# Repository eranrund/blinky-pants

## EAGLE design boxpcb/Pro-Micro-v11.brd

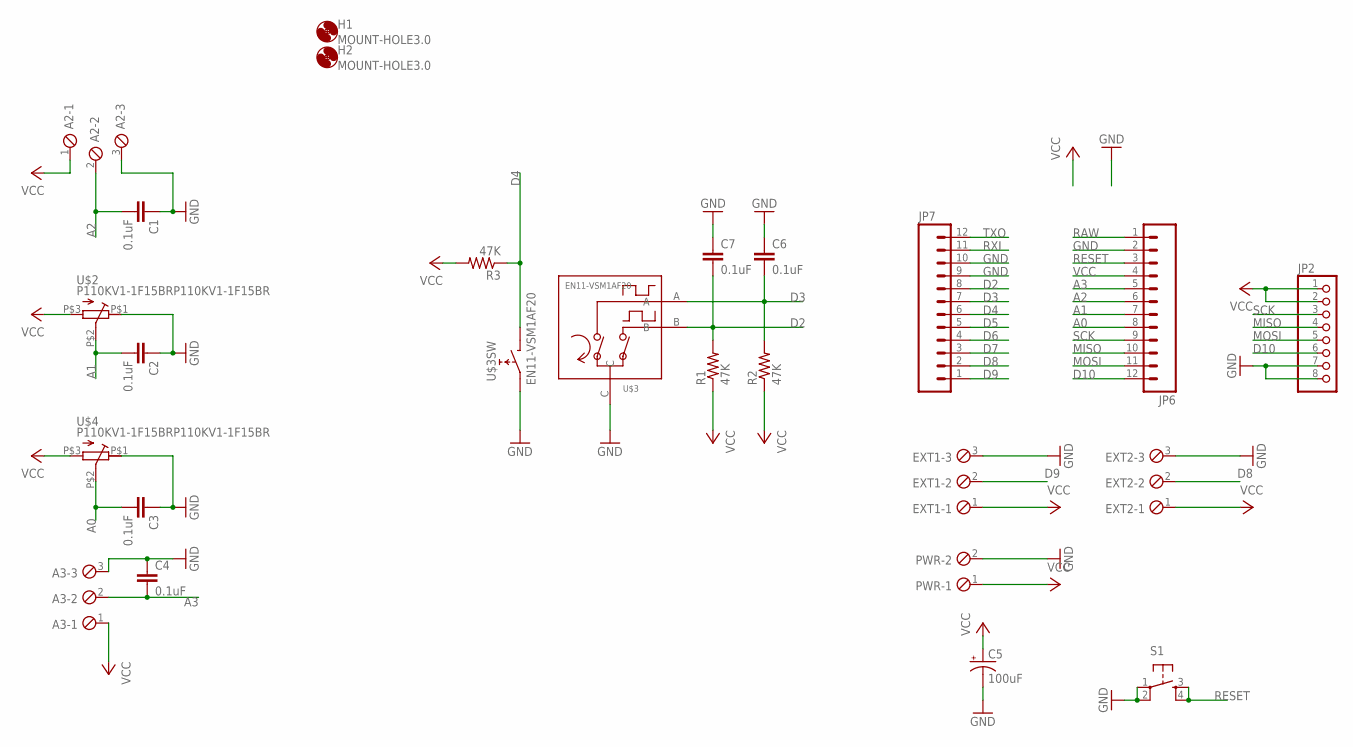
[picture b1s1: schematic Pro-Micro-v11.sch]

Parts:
A2, A3: MPT3; 3POL254
C1, C2, C3, C4: 0.1uF; C025-025X050
C5: 100uF; E3,5-8
C6, C7: 0.1uF; C025-024X044
EXT1, EXT2: MPT3; 3POL254
H1, H2: MOUNT-HOLE3.0; 3,0
JP2: HEADER-1X8; 1X08_OVAL
JP6, JP7: M12PTH; 1X12
PWR: MPT2; 2POL254
R1, R2, R3: 47K; 0204/5
S1: TAC_SWITCHPTH; TACTILE-PTH
U$2, U$4: P110KV1-1F15BRP110KV1-1F15BR; P110KV1-1F15BR
U$3: EN11-VSM1AF20; EN11-VS*

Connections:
A0: C3.2, JP6.8, U$4.P$2 (S)
A1: C2.2, JP6.7, U$2.P$2 (S)
A2: A2.2, C1.2, JP6.6
A3: A3.2, C4.2, JP6.5
D2: C7.2, JP7.8, R1.2, U$3.B
D3: C6.2, JP7.7, R2.2, U$3.A
D4: JP7.6, R3.1, U$3.E
D5: JP7.5
D6: JP7.4
D7: JP7.3
D8: EXT2.2, JP7.2
D9: EXT1.2, JP7.1
D10: JP2.6, JP6.12
GND: A2.3, A3.3, C1.1, C2.1, C3.1, C4.1, C5.-, C6.1, C7.1, EXT1.3, EXT2.3, JP2.7, JP2.8, JP6.2, JP7.9, JP7.10, PWR.2, S1.1, S1.2, U$2.P$1 (A), U$3.C, U$3.D, U$4.P$1 (A)
MISO: JP2.4, JP6.10
MOSI: JP2.5, JP6.11
RAW: JP6.1
RESET: JP6.3, S1.3, S1.4
RXI: JP7.11
SCK: JP2.3, JP6.9
TXO: JP7.12
VCC: A2.1, A3.1, C5.+, EXT1.1, EXT2.1, JP2.1, JP2.2, JP6.4, PWR.1, R1.1, R2.1, R3.2, U$2.P$3 (E), U$4.P$3 (E)

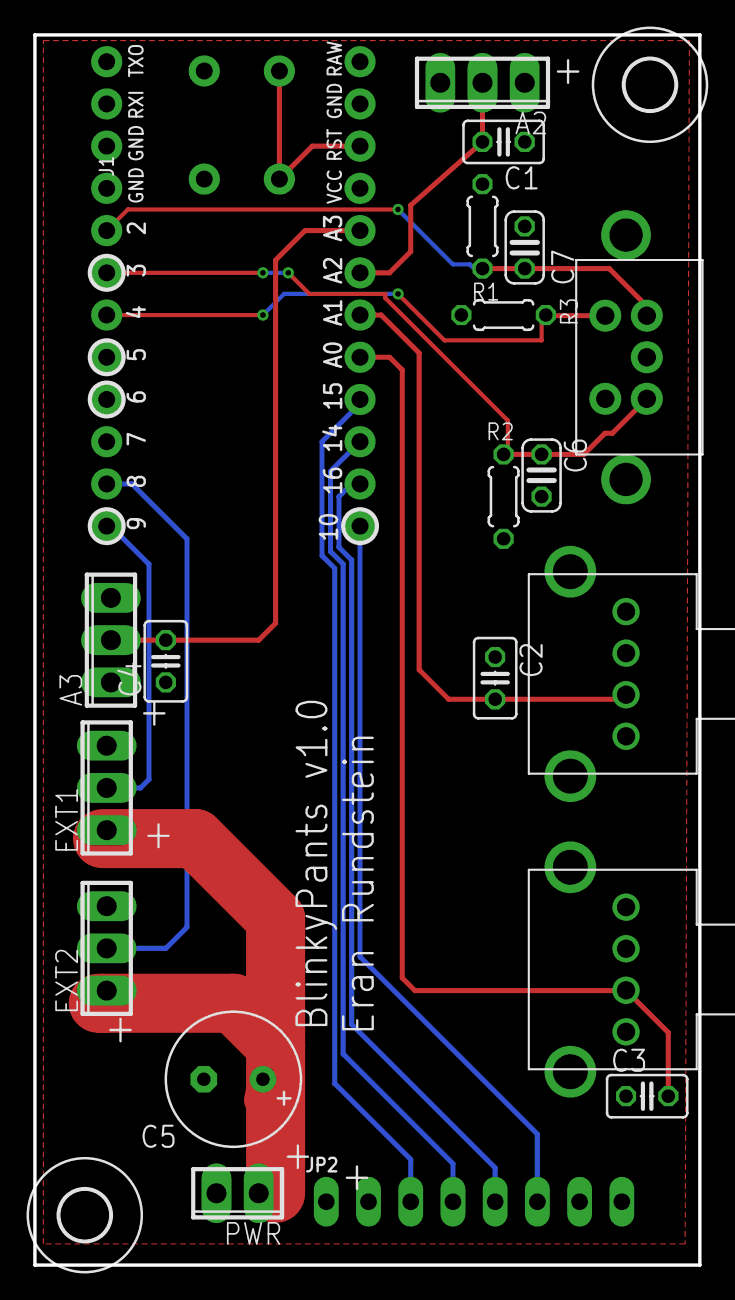
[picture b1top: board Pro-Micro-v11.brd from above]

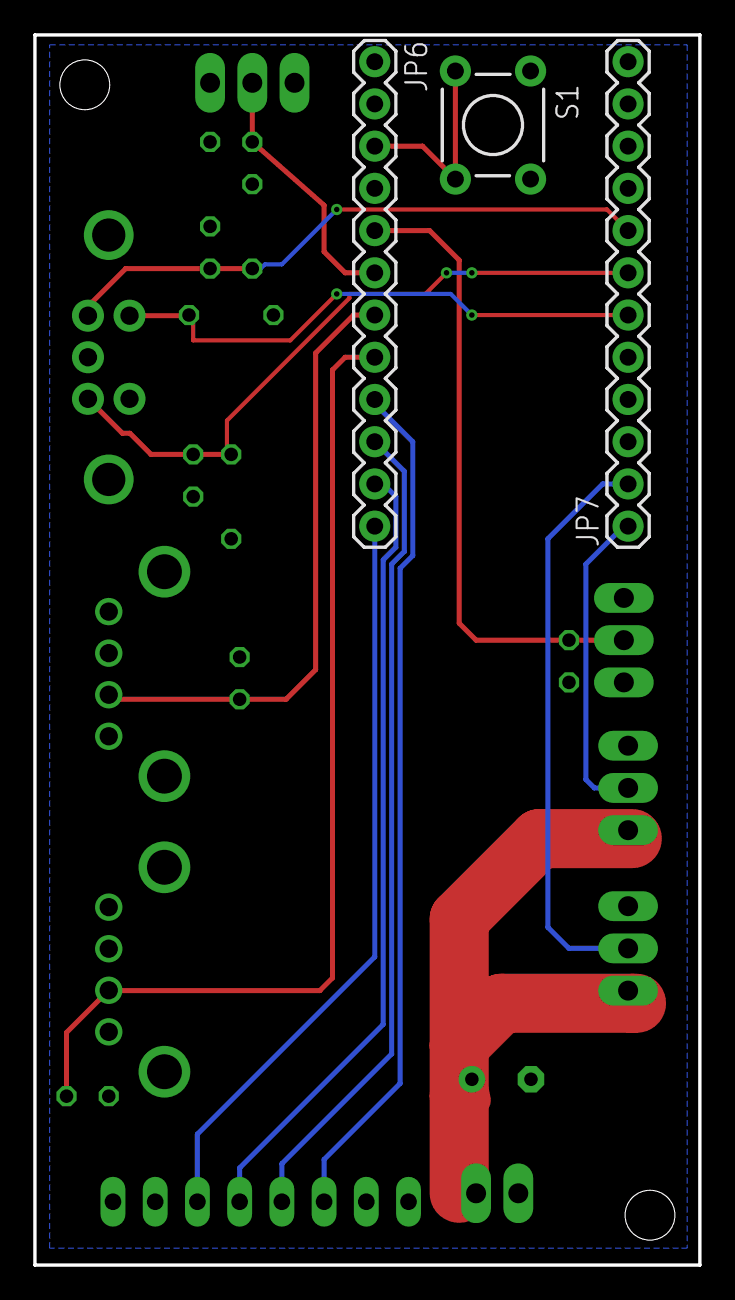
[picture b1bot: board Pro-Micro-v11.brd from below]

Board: 2 copper layers, 40.0 x 74.0 mm, 24 parts (3 on the bottom side), 16 nets.

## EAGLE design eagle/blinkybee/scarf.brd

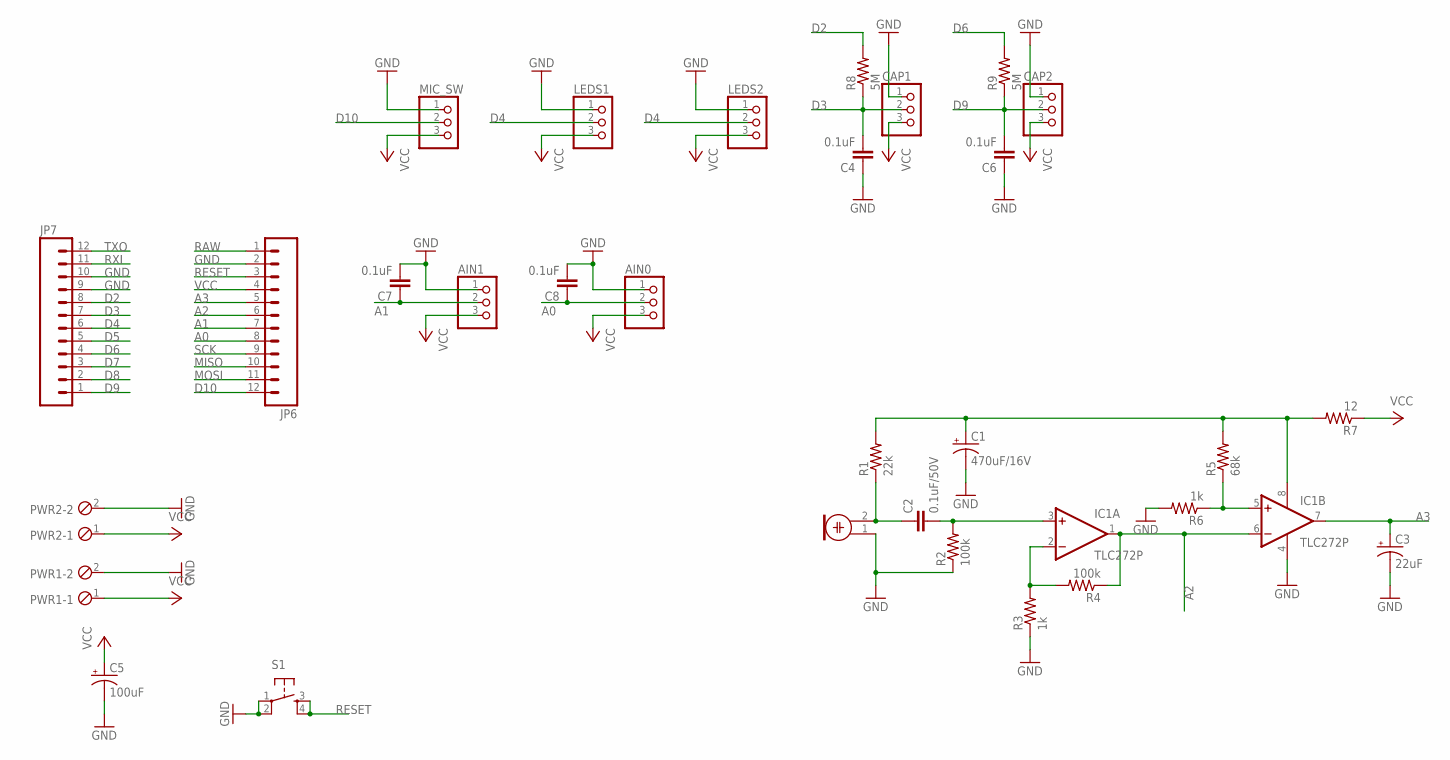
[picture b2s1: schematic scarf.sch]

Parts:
AIN0, AIN1: HEADER-1X3ROUND; 1X03_ROUND
C1: 470uF/16V; E2,5-6
C2: 0.1uF/50V; C050-025X075
C3: 22uF; E2,5-6
C4, C6, C7, C8: 0.1uF; C025-025X050
C5: 100uF; E3,5-8
CAP1, CAP2: HEADER-1X3ROUND; 1X03_ROUND
IC1: TLC272P; DIL08
JP6, JP7: M12PTH; 1X12
LEDS1, LEDS2: PINHD-1X3; 1X03
M1: ELECTRET_MICROPHON-WM.64PN; WM-64PN
MIC_SW: HEADER-1X3ROUND; 1X03_ROUND
PWR1, PWR2: MPT2; 2POL254
R1: 22k; 0204/7
R2, R4: 100k; 0204/7
R3, R6: 1k; 0204/7
R5: 68k; 0204/7
R7: 12; 0204/7
R8, R9: 5M; 0204/7
S1: TAC_SWITCHPTH; TACTILE-PTH

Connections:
A0: AIN0.2, C8.1, JP6.8
A1: AIN1.2, C7.1, JP6.7
A2: IC1.1 (OUT), IC1.6 (-IN), JP6.6, R4.1
A3: C3.+, IC1.7 (OUT), JP6.5
D2: JP7.8, R8.2
D3: C4.2, CAP1.2, JP7.7, R8.1
D4: JP7.6, LEDS1.2, LEDS2.2
D5: JP7.5
D6: JP7.4, R9.2
D7: JP7.3
D8: JP7.2
D9: C6.2, CAP2.2, JP7.1, R9.1
D10: JP6.12, MIC_SW.2
GND: AIN0.1, AIN1.1, C1.-, C3.-, C4.1, C5.-, C6.1, C7.2, C8.2, CAP1.1, CAP2.1, IC1.4 (V-), JP6.2, JP7.9, JP7.10, LEDS1.1, LEDS2.1, M1.1, MIC_SW.1, PWR1.2, PWR2.2, R2.1, R3.1, R6.2, S1.1, S1.2
MISO: JP6.10
MOSI: JP6.11
unnamed: C2.2, IC1.3 (+IN), R2.2
unnamed: C2.1, M1.2, R1.1
unnamed: IC1.2 (-IN), R3.2, R4.2
unnamed: IC1.5 (+IN), R5.1, R6.1
unnamed: C1.+, IC1.8 (V+), R1.2, R5.2, R7.2
RAW: JP6.1
RESET: JP6.3, S1.3, S1.4
RXI: JP7.11
SCK: JP6.9
TXO: JP7.12
VCC: AIN0.3, AIN1.3, C5.+, CAP1.3, CAP2.3, JP6.4, LEDS1.3, LEDS2.3, MIC_SW.3, PWR1.1, PWR2.1, R7.1

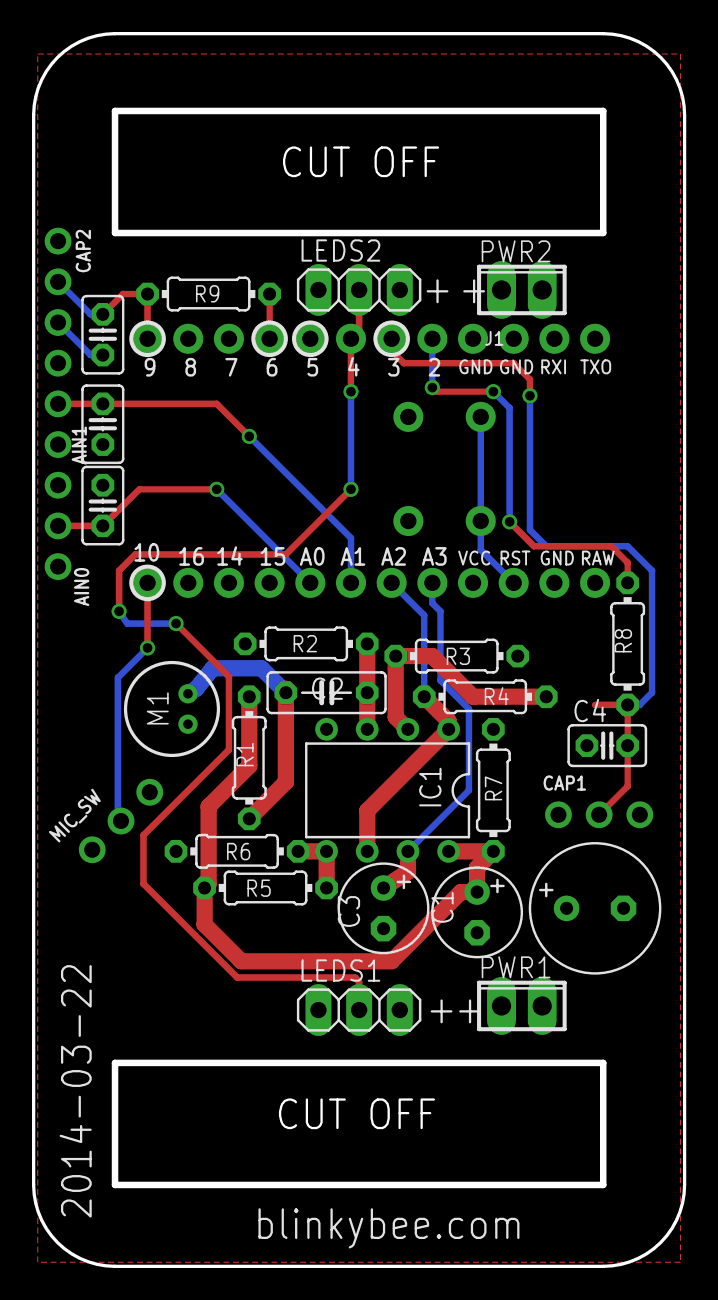
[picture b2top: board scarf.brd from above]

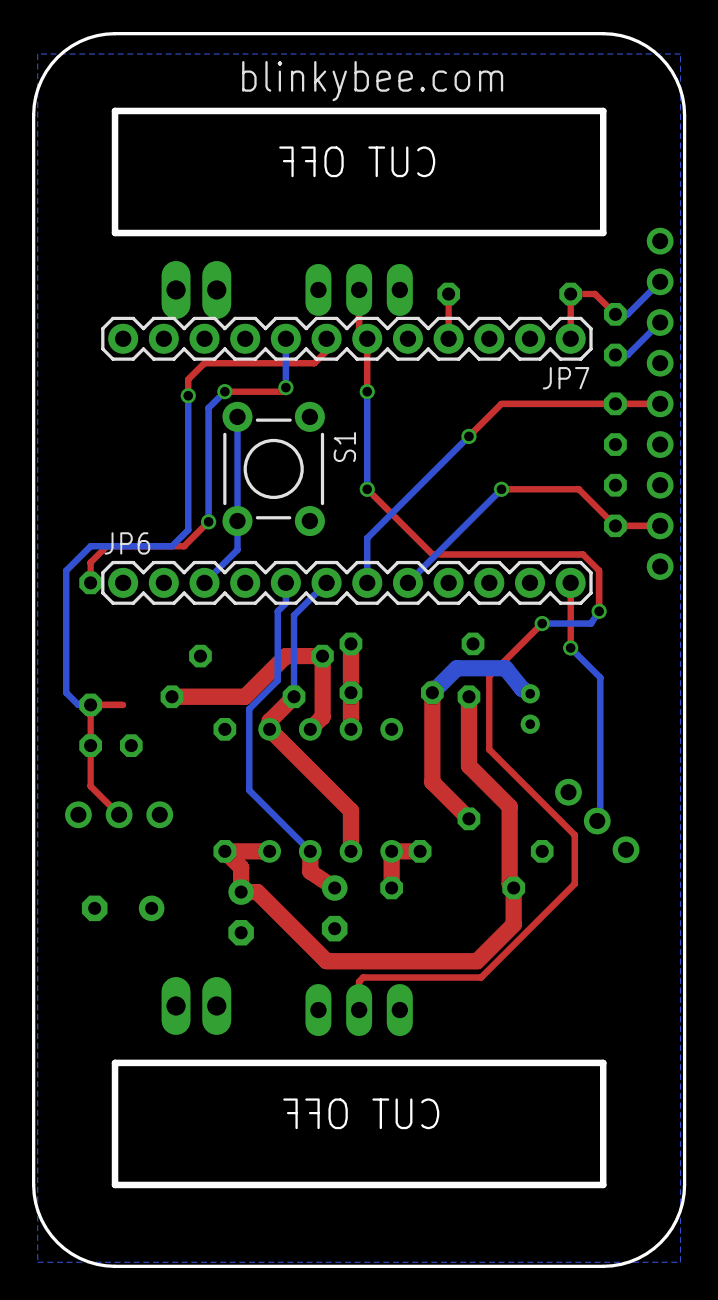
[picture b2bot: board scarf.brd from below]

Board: 2 copper layers, 40.6 x 77.0 mm, 31 parts (3 on the bottom side), 18 nets.

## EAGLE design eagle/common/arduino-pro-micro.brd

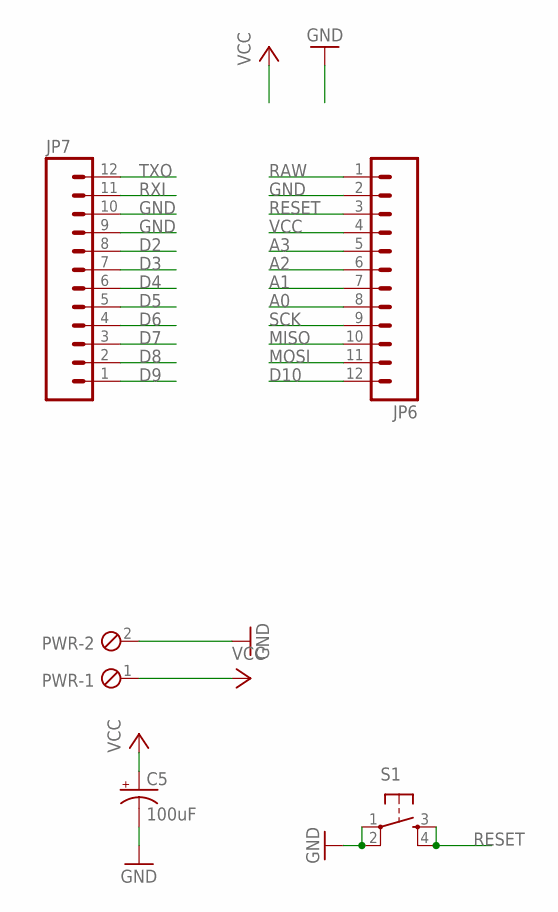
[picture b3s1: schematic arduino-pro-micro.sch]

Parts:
C5: 100uF; E3,5-8
JP6, JP7: M12PTH; 1X12
PWR: MPT2; 2POL254
S1: TAC_SWITCHPTH; TACTILE-PTH

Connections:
A0: JP6.8
A1: JP6.7
A2: JP6.6
A3: JP6.5
D2: JP7.8
D3: JP7.7
D4: JP7.6
D5: JP7.5
D6: JP7.4
D7: JP7.3
D8: JP7.2
D9: JP7.1
D10: JP6.12
GND: C5.-, JP6.2, JP7.9, JP7.10, PWR.2, S1.1, S1.2
MISO: JP6.10
MOSI: JP6.11
RAW: JP6.1
RESET: JP6.3, S1.3, S1.4
RXI: JP7.11
SCK: JP6.9
TXO: JP7.12
VCC: C5.+, JP6.4, PWR.1

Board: 2 copper layers, 5 parts (3 on the bottom side), 3 nets, no tracks yet.

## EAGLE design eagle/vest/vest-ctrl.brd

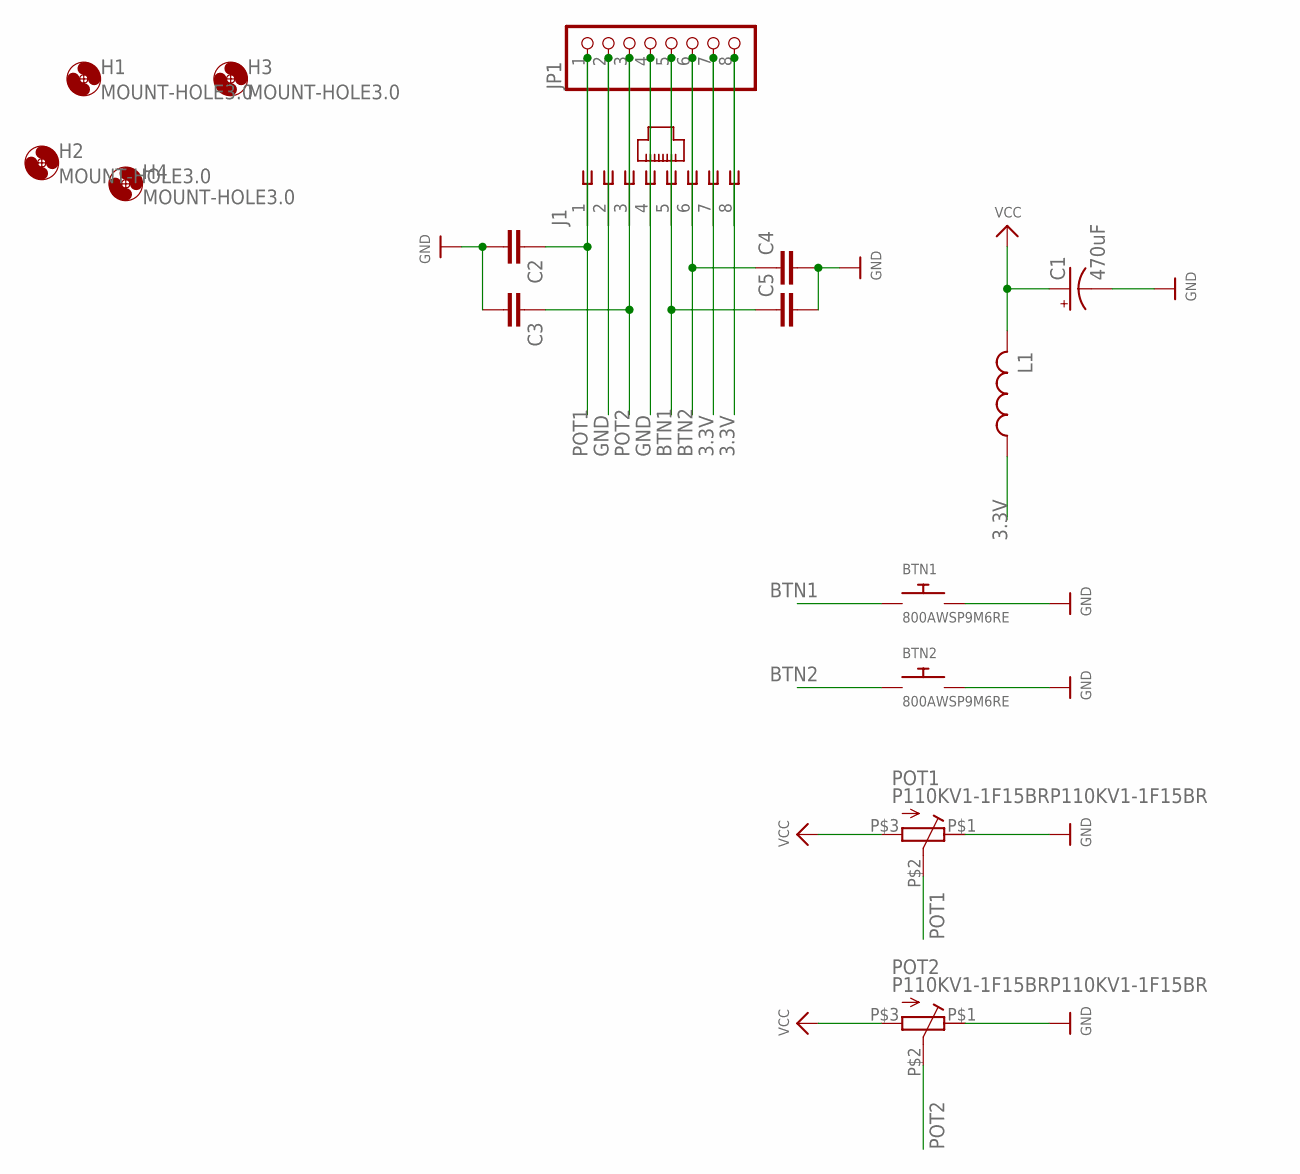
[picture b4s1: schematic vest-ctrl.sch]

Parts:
BTN1, BTN2: 800AWSP9M6RE
C1: 470uF; TT2D5L
C2, C3, C4, C5: C-EU025-025X050; C025-025X050
H1, H2, H3, H4: MOUNT-HOLE3.0; 3,0
J1: 215877-4
JP1: HEADER-1X870MIL; 1X08_ROUND_70
L1: L-US0207/10; 0207/10
POT1, POT2: P110KV1-1F15BRP110KV1-1F15BR; P110KV1-1F15BR

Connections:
3.3V: J1.7, J1.8, JP1.7, JP1.8, L1.1
BTN1: BTN1.SW1, C5.1, J1.5, JP1.5
BTN2: BTN2.SW1, C4.1, J1.6, JP1.6
GND: BTN1.SW2, BTN2.SW2, C1.-, C2.2, C3.2, C4.2, C5.2, J1.2, J1.4, JP1.2, JP1.4, POT1.P$1 (A), POT2.P$1 (A)
POT1: C2.1, J1.1, JP1.1, POT1.P$2 (S)
POT2: C3.1, J1.3, JP1.3, POT2.P$2 (S)
VCC: C1.+, L1.2, POT1.P$3 (E), POT2.P$3 (E)

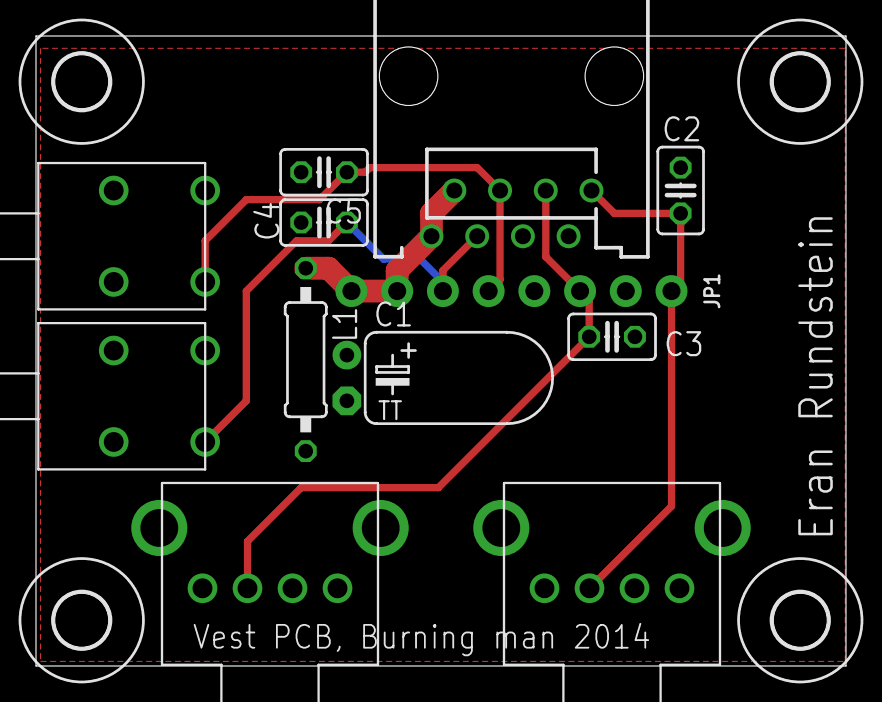
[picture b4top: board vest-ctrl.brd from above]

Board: 2 copper layers, 45.0 x 35.0 mm, 16 parts (0 on the bottom side), 7 nets.

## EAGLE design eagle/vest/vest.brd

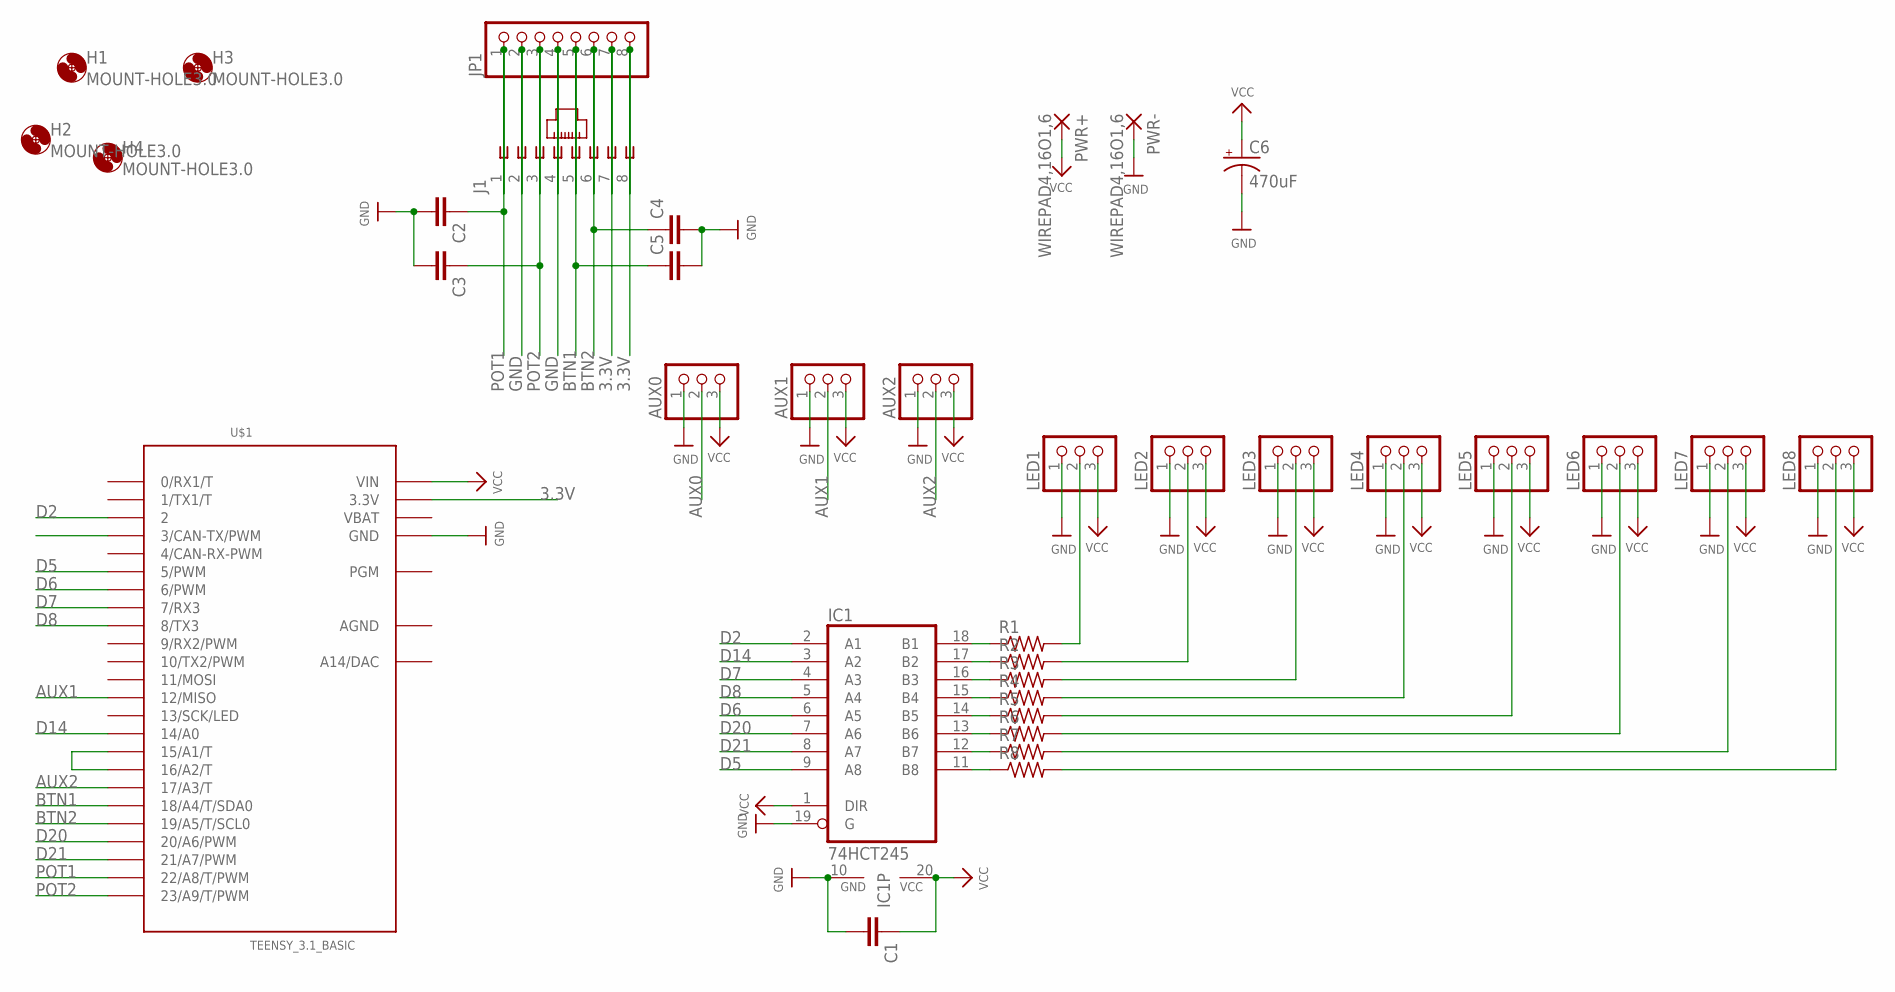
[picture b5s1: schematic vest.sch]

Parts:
AUX0, AUX1, AUX2: HEADER-1X3; 1X03_OVAL
C1, C2, C3, C4, C5: C-EU025-025X050; C025-025X050
C6: 470uF; TT2D7L
H1, H2, H3, H4: MOUNT-HOLE3.0; 3,0
IC1: 74HCT245; DIL20
J1: 215877-4
JP1: HEADER-1X870MIL; 1X08_ROUND_70
LED1, LED2, LED3, LED4, LED5, LED6, LED7, LED8: HEADER-1X3; 1X03_OVAL
PWR+: WIREPAD4,16O1,6; 4,16O1,6
PWR-: WIREPAD4,16O1,6; 4,16O1,6
R1, R2, R3, R4, R5, R6, R7, R8: R-US_0204/7; 0204/7
U$1: TEENSY_3.1_BASIC

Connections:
3.3V: J1.7, J1.8, JP1.7, JP1.8, U$1.3.3V, U$1.3.3V1 (3.3V)
AGND: U$1.AGND
AUX0: AUX0.2, U$1.3 (3/CAN-TX/PWM)
AUX1: AUX1.2, U$1.12 (12/MISO)
AUX2: AUX2.2, U$1.17/A3 (17/A3/T)
BTN1: C5.1, J1.5, JP1.5, U$1.18/A4 (18/A4/T/SDA0)
BTN2: C4.1, J1.6, JP1.6, U$1.19/A5 (19/A5/T/SCL0)
D2: IC1.2 (A1), U$1.2
D5: IC1.9 (A8), U$1.5 (5/PWM)
D6: IC1.6 (A5), U$1.6 (6/PWM)
D7: IC1.4 (A3), U$1.7 (7/RX3)
D8: IC1.5 (A4), U$1.8 (8/TX3)
D14: IC1.3 (A2), U$1.14/A0
D20: IC1.7 (A6), U$1.20/A6 (20/A6/PWM)
D21: IC1.8 (A7), U$1.21/A7 (21/A7/PWM)
GND: AUX0.1, AUX1.1, AUX2.1, C1.2, C2.2, C3.2, C4.2, C5.2, C6.-, IC1.10 (GND), IC1.19 (G), J1.2, J1.4, JP1.2, JP1.4, LED1.1, LED2.1, LED3.1, LED4.1, LED5.1, LED6.1, LED7.1, LED8.1, PWR-.1, U$1.GND, U$1.GND1 (GND)
unnamed: U$1.15/A1 (15/A1/T), U$1.16/A2 (16/A2/T)
unnamed: IC1.11 (B8), R8.1
unnamed: IC1.18 (B1), R1.1
unnamed: IC1.17 (B2), R2.1
unnamed: IC1.16 (B3), R3.1
unnamed: IC1.15 (B4), R4.1
unnamed: IC1.14 (B5), R5.1
unnamed: IC1.13 (B6), R6.1
unnamed: IC1.12 (B7), R7.1
unnamed: LED1.2, R1.2
unnamed: LED2.2, R2.2
unnamed: LED3.2, R3.2
unnamed: LED4.2, R4.2
unnamed: LED5.2, R5.2
unnamed: LED6.2, R6.2
unnamed: LED7.2, R7.2
unnamed: LED8.2, R8.2
POT1: C2.1, J1.1, JP1.1, U$1.22/A8 (22/A8/T/PWM)
POT2: C3.1, J1.3, JP1.3, U$1.23/A9 (23/A9/T/PWM)
VBAT: U$1.VBAT
VCC: AUX0.3, AUX1.3, AUX2.3, C1.1, C6.+, IC1.1 (DIR), IC1.20 (VCC), LED1.3, LED2.3, LED3.3, LED4.3, LED5.3, LED6.3, LED7.3, LED8.3, PWR+.1, U$1.VIN

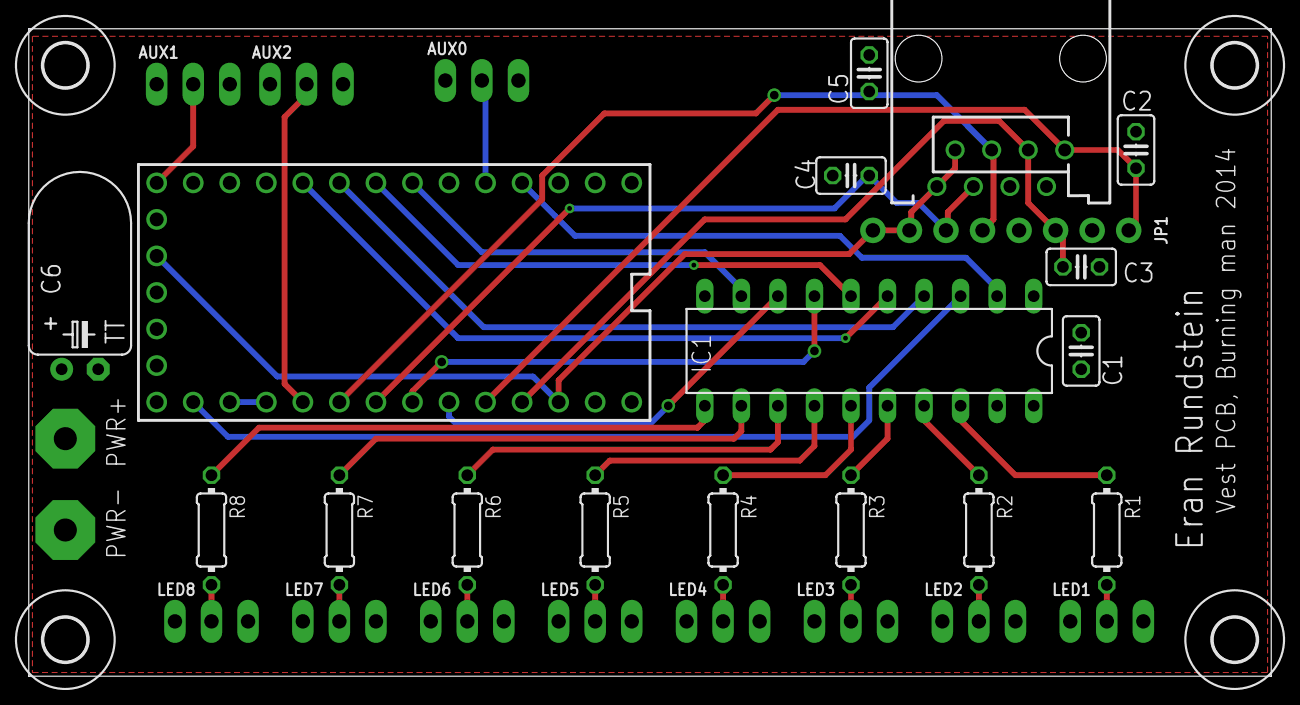
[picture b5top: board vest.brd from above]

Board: 2 copper layers, 86.4 x 45.0 mm, 35 parts (0 on the bottom side), 35 nets.

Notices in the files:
parts and their libraries:
SparkFun-Electromechanical: Licensing: CC v3.0 Share-Alike You are welcome to use this library for commercial purposes.
microbuilder: This work is placed in the public domain, and may be freely used for commercial and non-commercial work with the following conditions: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
